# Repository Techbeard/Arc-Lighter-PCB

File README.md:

# Arc-Lighter-PCB
A replacement PCB for an arc lighter

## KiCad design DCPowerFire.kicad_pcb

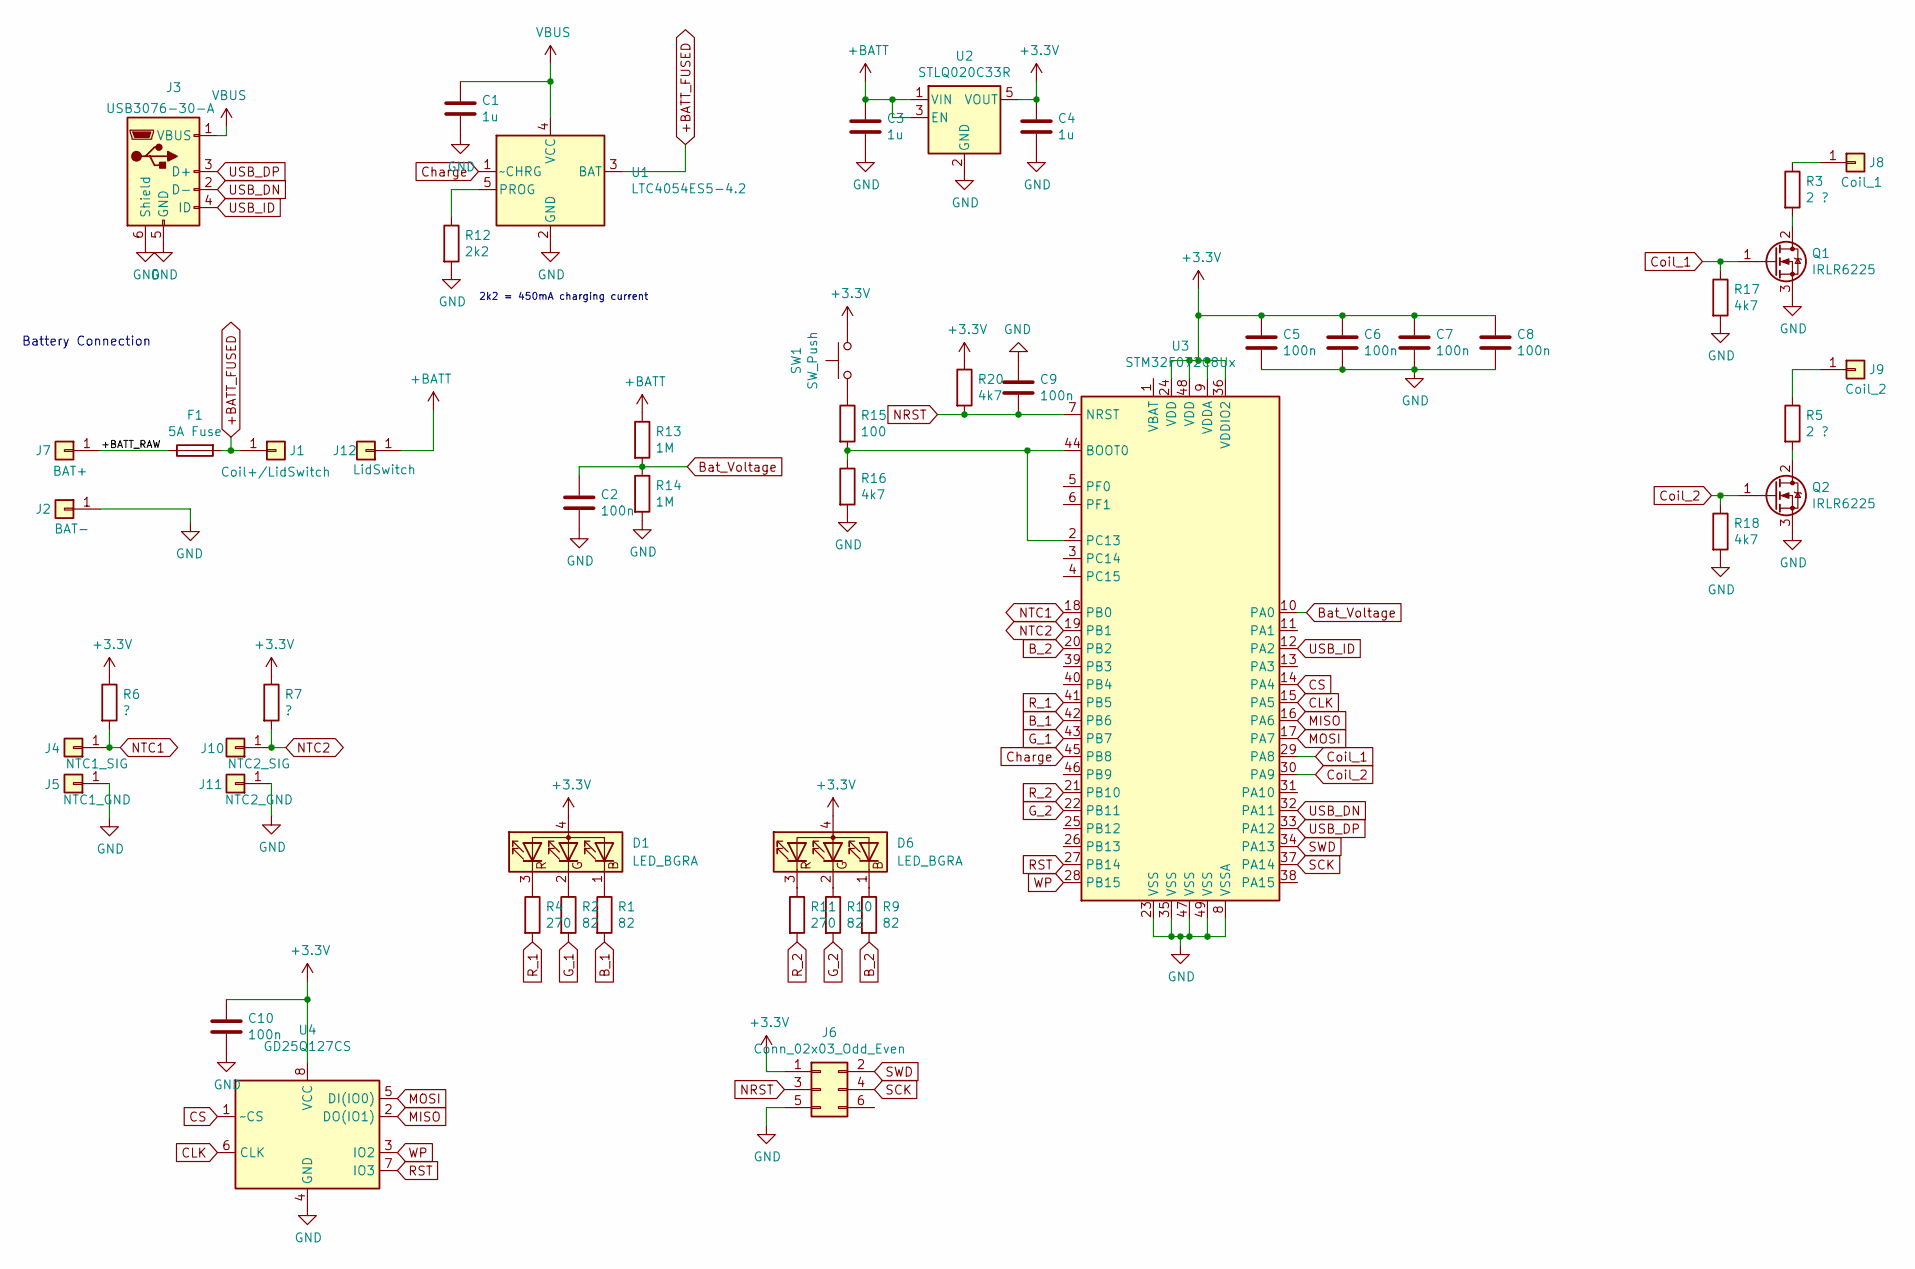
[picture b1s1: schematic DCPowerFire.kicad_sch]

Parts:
C1, C3, C4: 1u; C_0402_1005Metric
C2, C5, C6, C7, C8, C9, C10: 100n; C_0402_1005Metric
D1, D6: LED_BGRA; RGB_0404
F1: 5A Fuse; Fuse_0603_1608Metric
J1: Coil+/LidSwitch; TestPoint_Pad_1.0x1.0mm_NoSilk
J2: BAT-; TestPoint_Pad_1.0x1.0mm_NoSilk
J3: USB3076-30-A; USB_Micro-B_GCT_USB3076-30-A
J4: NTC1_SIG; TestPoint_Pad_1.0x1.0mm_NoSilk
J5: NTC1_GND; TestPoint_Pad_1.0x1.0mm_NoSilk
J6: Conn_02x03_Odd_Even; Tag-Connect_TC2030-IDC-NL_2x03_P1.27mm_Vertical
J7: BAT+; TestPoint_Pad_1.0x1.0mm_NoSilk
J8: Coil_1; TestPoint_Pad_1.0x1.0mm_NoSilk
J9: Coil_2; TestPoint_Pad_1.0x1.0mm_NoSilk
J10: NTC2_SIG; TestPoint_Pad_1.0x1.0mm_NoSilk
J11: NTC2_GND; TestPoint_Pad_1.0x1.0mm_NoSilk
J12: LidSwitch; TestPoint_Pad_1.0x1.0mm_NoSilk
Q1, Q2: IRLR6225; TO-252-2
R1, R2, R9, R10: 82; R_0402_1005Metric
R3, R5: 2 ?; R_1206_3216Metric
R4, R11: 270; R_0402_1005Metric
R6, R7: ?; R_0402_1005Metric
R12: 2k2; R_0402_1005Metric
R13, R14: 1M; R_0402_1005Metric
R15: 100; R_0402_1005Metric
R16, R17, R18, R20: 4k7; R_0402_1005Metric
SW1: SW_Push; SW_SPST_TL3342
U1: LTC4054ES5-4.2; TSOT-23-5
U2: STLQ020C33R; SOT-23-5
U3: STM32F072C8Ux; QFN-48-1EP_7x7mm_P0.5mm_EP5.6x5.6mm
U4: GD25Q127CS; SOIC-8_5.23x5.23mm_P1.27mm

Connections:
+3V3: C4.1, C5.1, C6.1, C7.1, C8.1, C10.1, D1.4 (A), D6.4 (A), J6.1, R6.1, R7.1, R20.1, SW1.2, U2.5 (VOUT), U3.9 (VDDA), U3.24 (VDD), U3.36 (VDDIO2), U3.48 (VDD), U4.8 (VCC)
+BATT: C3.1, J12.1, R13.1, U2.1 (VIN), U2.3 (EN)
+BATT_FUSED: F1.2, J1.1, U1.3 (BAT)
/+BATT_RAW: F1.1, J7.1
B_1: R1.2, U3.42 (PB6)
B_2: R9.2, U3.20 (PB2)
Bat_Voltage: C2.1, R13.2, R14.1, U3.10 (PA0)
CLK: U3.15 (PA5), U4.6 (CLK)
CS: U3.14 (PA4), U4.1 (~CS)
Charge: U1.1 (~CHRG), U3.45 (PB8)
Coil_1: Q1.1 (G), R17.1, U3.29 (PA8)
Coil_2: Q2.1 (G), R18.1, U3.30 (PA9)
GND: C1.2, C2.2, C3.2, C4.2, C5.2, C6.2, C7.2, C8.2, C9.1, C10.2, J2.1, J3.5 (GND), J3.6 (Shield), J5.1, J6.5, J11.1, Q1.3 (S), Q2.3 (S), R12.2, R14.2, R16.2, R17.2, R18.2, U1.2 (GND), U2.2 (GND), U3.8 (VSSA), U3.23 (VSS), U3.35 (VSS), U3.47 (VSS), U3.49 (VSS), U4.4 (GND)
G_1: R2.2, U3.43 (PB7)
G_2: R10.2, U3.22 (PB11)
MISO: U3.16 (PA6), U4.2 (DO(IO1))
MOSI: U3.17 (PA7), U4.5 (DI(IO0))
NRST: C9.2, J6.3, R20.2, U3.7 (NRST)
NTC1: J4.1, R6.2, U3.18 (PB0)
NTC2: J10.1, R7.2, U3.19 (PB1)
unnamed: D1.1 (BK), R1.1
unnamed: D1.2 (GK), R2.1
unnamed: D1.3 (RK), R4.1
unnamed: D6.1 (BK), R9.1
unnamed: D6.2 (GK), R10.1
unnamed: D6.3 (RK), R11.1
unnamed: J8.1, R3.1
unnamed: J9.1, R5.1
unnamed: Q1.2 (D), R3.2
unnamed: Q2.2 (D), R5.2
unnamed: R12.1, U1.5 (PROG)
unnamed: R15.1, SW1.1
unnamed: R15.2, R16.1, U3.2 (PC13), U3.44 (BOOT0)
RST: U3.27 (PB14), U4.7 (IO3)
R_1: R4.2, U3.41 (PB5)
R_2: R11.2, U3.21 (PB10)
SCK: J6.4, U3.37 (PA14)
SWD: J6.2, U3.34 (PA13)
USB_DN: J3.2 (D-), U3.32 (PA11)
USB_DP: J3.3 (D+), U3.33 (PA12)
USB_ID: J3.4 (ID), U3.12 (PA2)
VBUS: C1.1, J3.1 (VBUS), U1.4 (VCC)
WP: U3.28 (PB15), U4.3 (IO2)

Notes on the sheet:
Battery Connection
2k2 = 450mA charging current

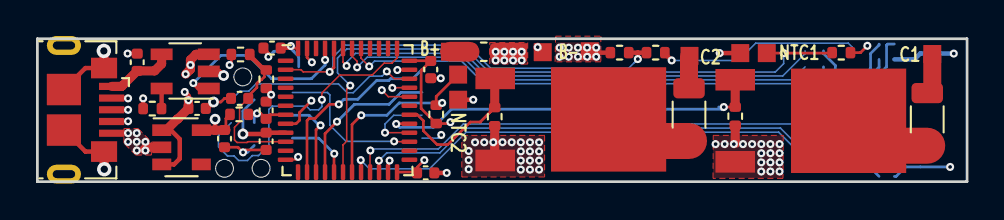
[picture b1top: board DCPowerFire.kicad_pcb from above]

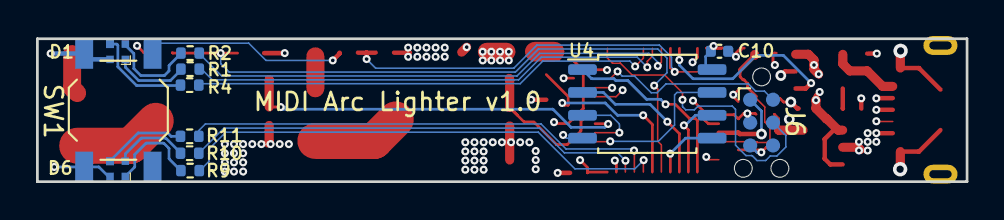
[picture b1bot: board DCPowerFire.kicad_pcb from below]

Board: 4 copper layers, 51.7 x 7.9 mm, 50 parts (12 on the bottom side), 43 nets.

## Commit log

2021-06-02 add files
2021-06-02 add schematic pdf
2021-07-07 edit things
2021-07-07 migrate project to current KiCad nightly
2021-07-07 finish USB ID trace and fix DRC errors
2021-07-07 add missing NTC connections & begin silkscreen
2021-07-07 add solder pad silkscreen
2021-07-08 bottom silkscreen
2021-07-08 add lid switch pads
2021-07-08 add title text
2021-07-16 generate fabrication outputs
2021-07-16 increase via sizes to 0.2/0.45mm
2021-07-30 add interactive BOM
2021-07-30 minor fixes noticed during first assembly
    resistor values, LED RGB mapping
